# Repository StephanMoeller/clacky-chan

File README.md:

# Clacky Chan 
Clacky Chan is a custom made prototype split keyboard for testing out communication using trrs cables between the halves.

It consists of:

- rp2040 pro micro
- pcb's for each half and wire attached thumb keys as I want the thumbs to be tented just slightly on relation to the finger area.
- No diodes. (it toke 20 mins of soldering for each side. It is not the last time I will try a diode-free design)

Its running my own firmware, zigmkay, which can be found here: https://github.com/StephanMoeller/zigmkay

# Black version - Unibody case

# Yellow version - Unibody case

# Yelow version - Split case

PCB gerber files for production can be found in clackychan/production/clackychan.zig

Following picture uses wiring, eg. GPIO 6 is used as the single col and all the row pins can be determined as well. The thumb keys are wired to the GPIO 6 and then I choose GPIO 10 in the corner as the row.

Ongoing OnShape repo with the tenting: https://cad.onshape.com/documents/76ee9714ee23fe3d9d1e73a4/w/b73638d5ae9d33482cab6d43/e/1ea8409974f0fb535c971db1

All my boards:

https://github.com/StephanMoeller/clacky-chan  
https://github.com/StephanMoeller/mike-typeson  
https://github.com/StephanMoeller/skinnypete32  
https://github.com/StephanMoeller/wilson26

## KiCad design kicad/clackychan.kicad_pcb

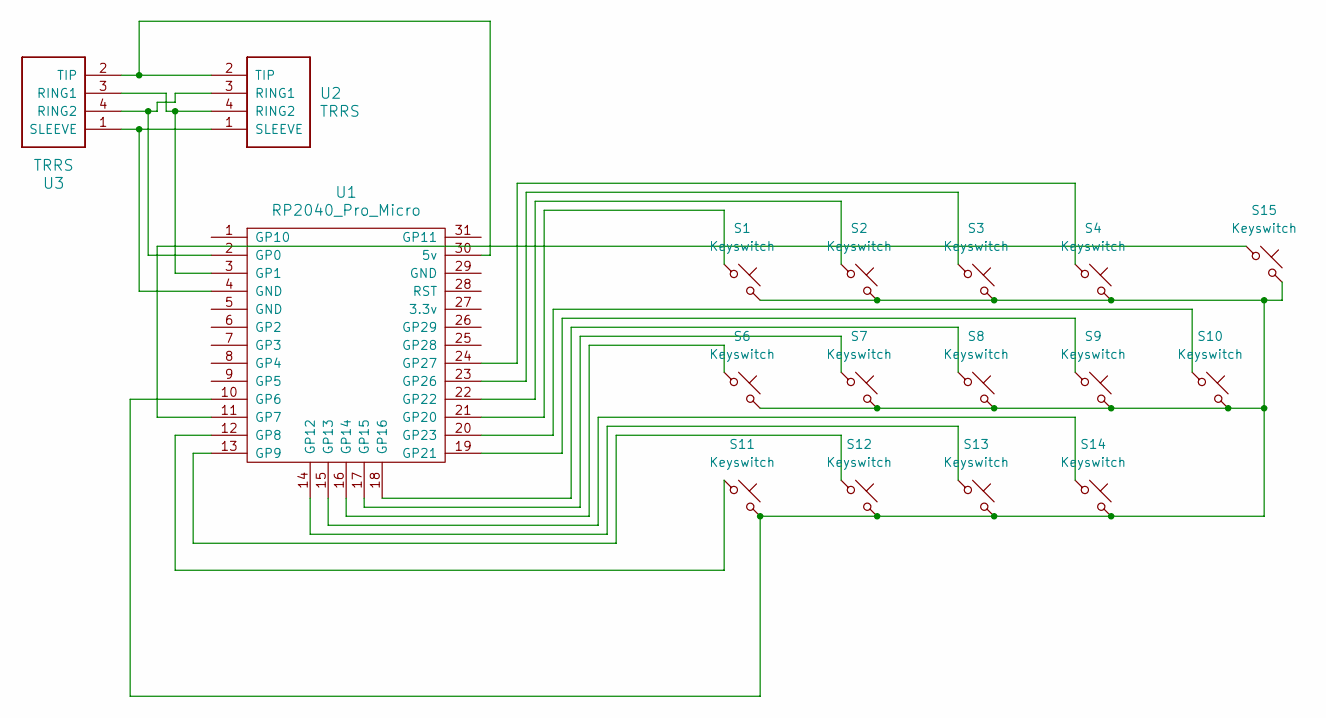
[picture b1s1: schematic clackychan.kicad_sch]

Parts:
S1, S2, S3, S4, S6, S7, S8, S9, S10, S11, S12, S13, S14, S15: Keyswitch; Kailh_socket_MX_reversible
U1: RP2040_Pro_Micro
U2, U3: TRRS; TRRS_PJ-320A

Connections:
unnamed: U1.30 (5v), U2.2 (TIP), U3.2 (TIP)
unnamed: U1.2 (GP0), U2.3 (RING1), U3.4 (RING2)
unnamed: U1.3 (GP1), U2.4 (RING2), U3.3 (RING1)
unnamed: S1.2, S2.2, S3.2, S4.2, S6.2, S7.2, S8.2, S9.2, S10.2, S11.2, S12.2, S13.2, S14.2, S15.2, U1.10 (GP6)
unnamed: S15.1, U1.11 (GP7)
unnamed: S11.1, U1.12 (GP8)
unnamed: S12.1, U1.13 (GP9)
unnamed: S13.1, U1.14 (GP12)
unnamed: S14.1, U1.15 (GP13)
unnamed: S6.1, U1.16 (GP14)
unnamed: S7.1, U1.17 (GP15)
unnamed: S8.1, U1.18 (GP16)
unnamed: S1.1, U1.21 (GP20)
unnamed: S9.1, U1.19 (GP21)
unnamed: S2.1, U1.22 (GP22)
unnamed: S10.1, U1.20 (GP23)
unnamed: S3.1, U1.23 (GP26)
unnamed: S4.1, U1.24 (GP27)
unnamed: U1.4 (GND), U2.1 (SLEEVE), U3.1 (SLEEVE)

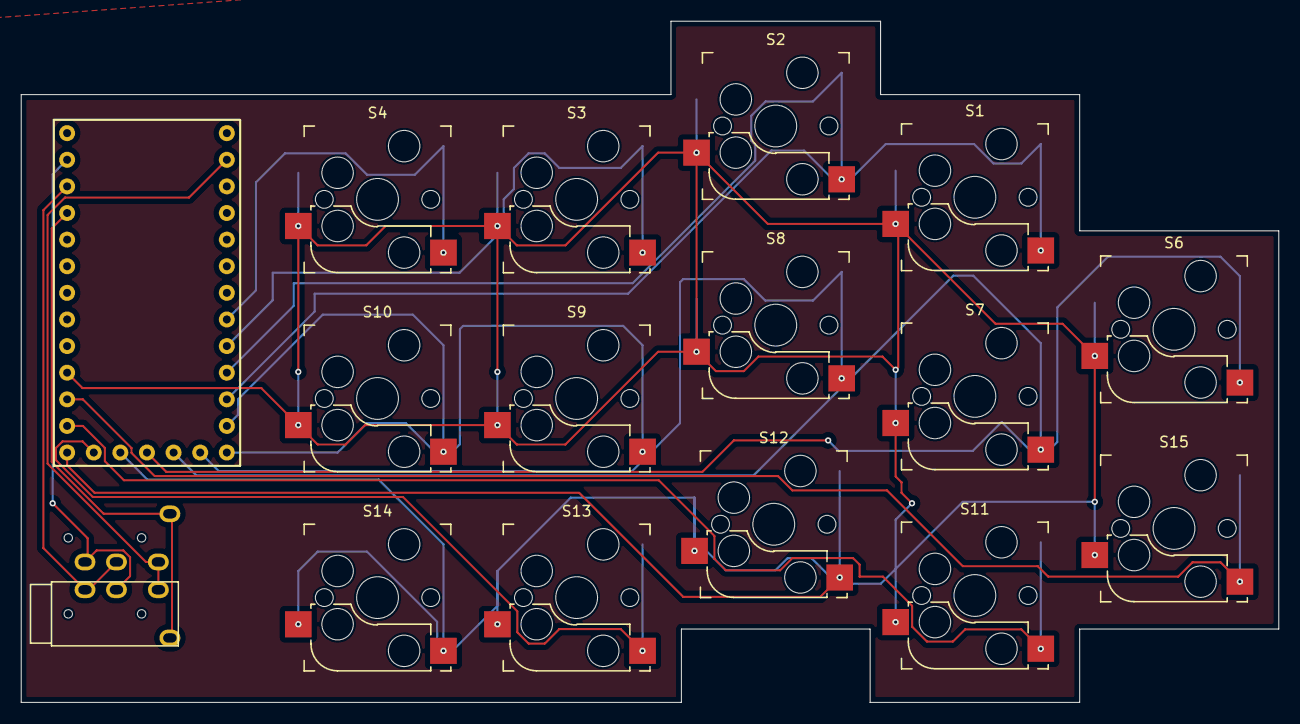
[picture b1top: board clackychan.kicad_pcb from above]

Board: 2 copper layers, 120.0 x 65.0 mm, 17 parts (1 on the bottom side), 19 nets.

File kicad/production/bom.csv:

Designator,Footprint,Quantity,Value,LCSC Part #
"S1, S10, S11, S12, S13, S14, S15, S2, S3, S4, S6, S7, S8, S9",Kailh_socket_MX_reversible,14,Keyswitch,
U1,RP2040_Pro_Micro,1,RP2040_Pro_Micro,
"U2, U3",TRRS_PJ-320A,2,TRRS,

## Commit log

2025-09-08 init files
2025-09-08 ordered gerber files added to git
2025-09-09 added a step file
2025-09-18 added stl
2025-09-18 renamed to kicad folder
2025-09-18 readme
2025-09-22 added unibody stl
2025-10-02 replaced wrong unibody case stl with right one
